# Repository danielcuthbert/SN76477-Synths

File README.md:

# The SN76477

Is a complex sound generator in the form of a monolithic chip produced by Texas Instruments in 1978. If you played ***Space Invadors*** or ***Sheriff*** it was this chip that gave you the sound effects. 

Being a kid of that time, and one interested in sounds and music, I felt building up a synthesisor around this chip was a good way to learn electronics. This repo is my own private Idaho and hopefully it's of some use to you. 

## Footprint

The chip is a 28-DIP and has the following measurements: 

- 1.78 Mm (0.07 In) Pitch
- 10.16 Mm (0.40 In) Span
- 25.15 X 8.89 X 5.08 Mm Body

Looking inside the chip via an X-ray is cool

I've created an Eagle library of the above, so you can just import it into your project and use it straight away. 

## Breakout Board

To make this work better with modern bread boards, you need a breakout board in order to connect all the various components up to. 

Eventually this will be turned into a fully-fledged PCB

## Pin Functions

1. Envelope Select (input)
2. Ground
1. External Noise Clock (input)
2. Noise Clock Resistor
1. Noise Filter Control Resistor
1. Noise Filter Control Capacitor
2. Decay Control Resistor
1. Attack/Decay Timing Capacitor
1. System Enable
1. Attack Control Resistor
1. Amplitude Control Resistor
1. Feedback Resistor
1. Audio Output
1. VCC
1. Envelope Select
1. Mixer Select C
1. Mixer Select A
1. Mixer Select B
1. One-Shot Control Resistor
1. One-Shot Control Capacitor
1. VCO Select
1. Super Low Frequency OSC. Control Capacitor
1. Super Low Frequency OSC. Control Resistor
1. Pitch Control
1. VCO Control Resistor
1. VCO Control Capacitor
1. External VCO Control
1. VREG

## How The Magic Happens

The SN76477 has the ability to create complex signal waveforms by combining a number of outputs. These outputs (low frequency oscillator and voltage-controlled VCO) added to a selected envelope and manipulating the signals attack, decay, sustain and release (ASDR) results in some beautiful noises.

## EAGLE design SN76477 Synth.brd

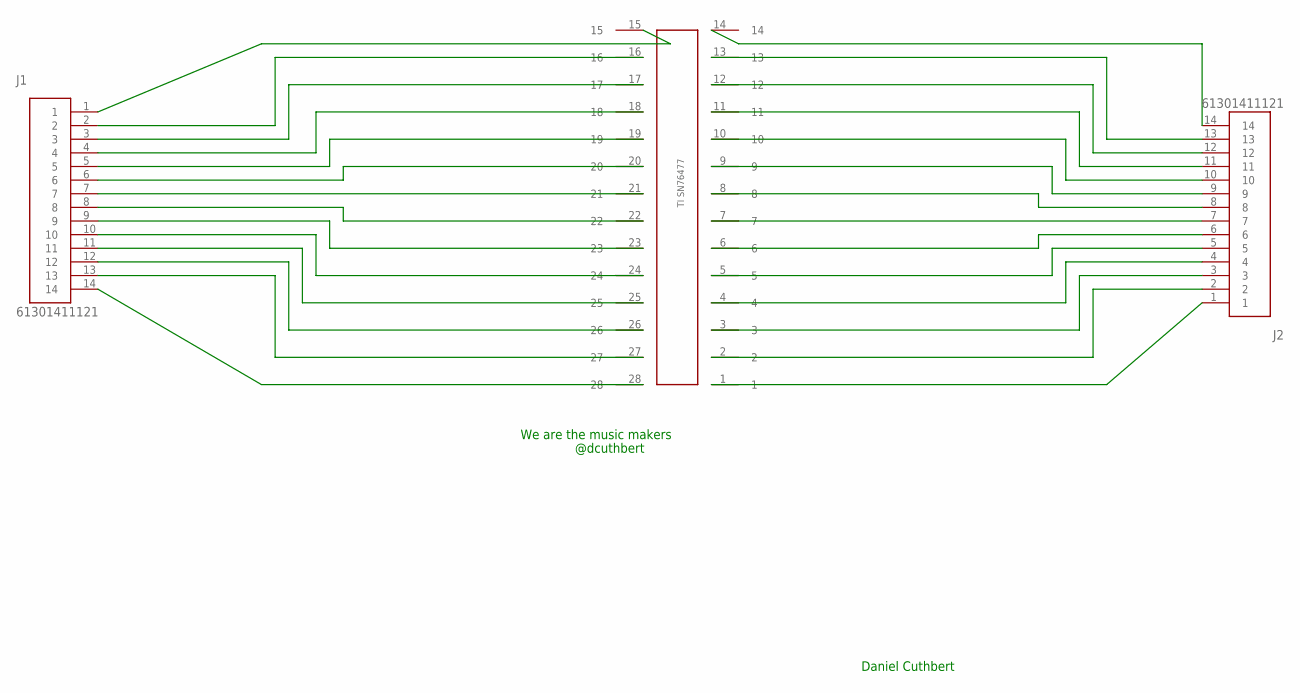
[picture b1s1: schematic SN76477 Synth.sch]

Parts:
J1, J2: 61301411121
U$1: SN76477NOISEGENERATORSN76477; SN76477NOISEGENERATOR

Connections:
unnamed: J2.1, U$1.1
unnamed: J2.2, U$1.2
unnamed: J2.3, U$1.3
unnamed: J2.4, U$1.4
unnamed: J2.5, U$1.5
unnamed: J2.6, U$1.6
unnamed: J2.7, U$1.7
unnamed: J2.8, U$1.8
unnamed: J2.9, U$1.9
unnamed: J2.10, U$1.10
unnamed: J2.11, U$1.11
unnamed: J2.12, U$1.12
unnamed: J2.13, U$1.13
unnamed: J2.14, U$1.14
unnamed: J1.1, U$1.15
unnamed: J1.14, U$1.28
unnamed: J1.2, U$1.16
unnamed: J1.13, U$1.27
unnamed: J1.12, U$1.26
unnamed: J1.11, U$1.25
unnamed: J1.10, U$1.24
unnamed: J1.9, U$1.23
unnamed: J1.8, U$1.22
unnamed: J1.7, U$1.21
unnamed: J1.6, U$1.20
unnamed: J1.5, U$1.19
unnamed: J1.4, U$1.18
unnamed: J1.3, U$1.17

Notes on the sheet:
Daniel Cuthbert
We are the music makers
@dcuthbert

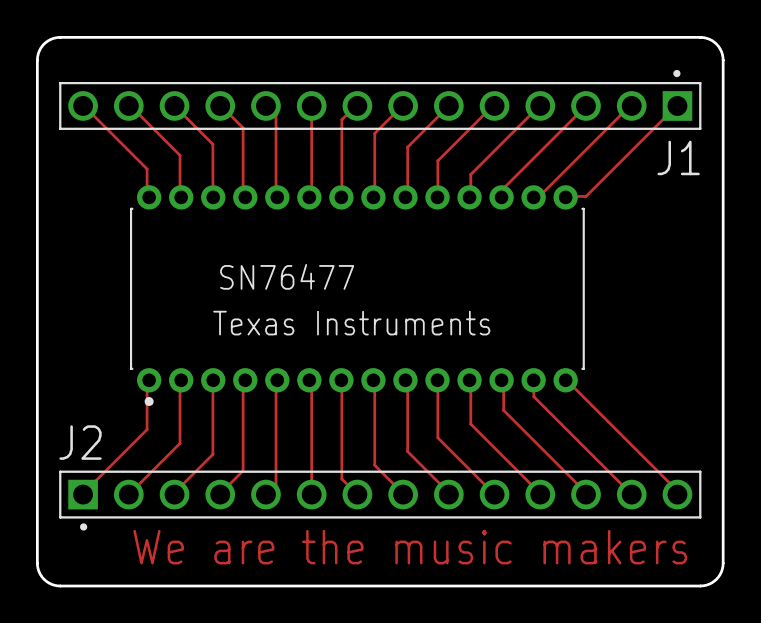
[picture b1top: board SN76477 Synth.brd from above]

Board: 2 copper layers, 38.1 x 30.5 mm, 3 parts (0 on the bottom side), 28 nets.

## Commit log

2020-02-03 Initial Commit of Eagle files
    Creating a basic breakout board for the SN76477 chip is needed
2020-02-03 Created README.md
2020-02-03 Added screenshots and Eagle Library
    Added the Eagle Library for the SN76477
2020-02-03 layout
2020-02-03 Added chip pinouts and howto
    What each pin on the chip does and how the chip makes noise.
